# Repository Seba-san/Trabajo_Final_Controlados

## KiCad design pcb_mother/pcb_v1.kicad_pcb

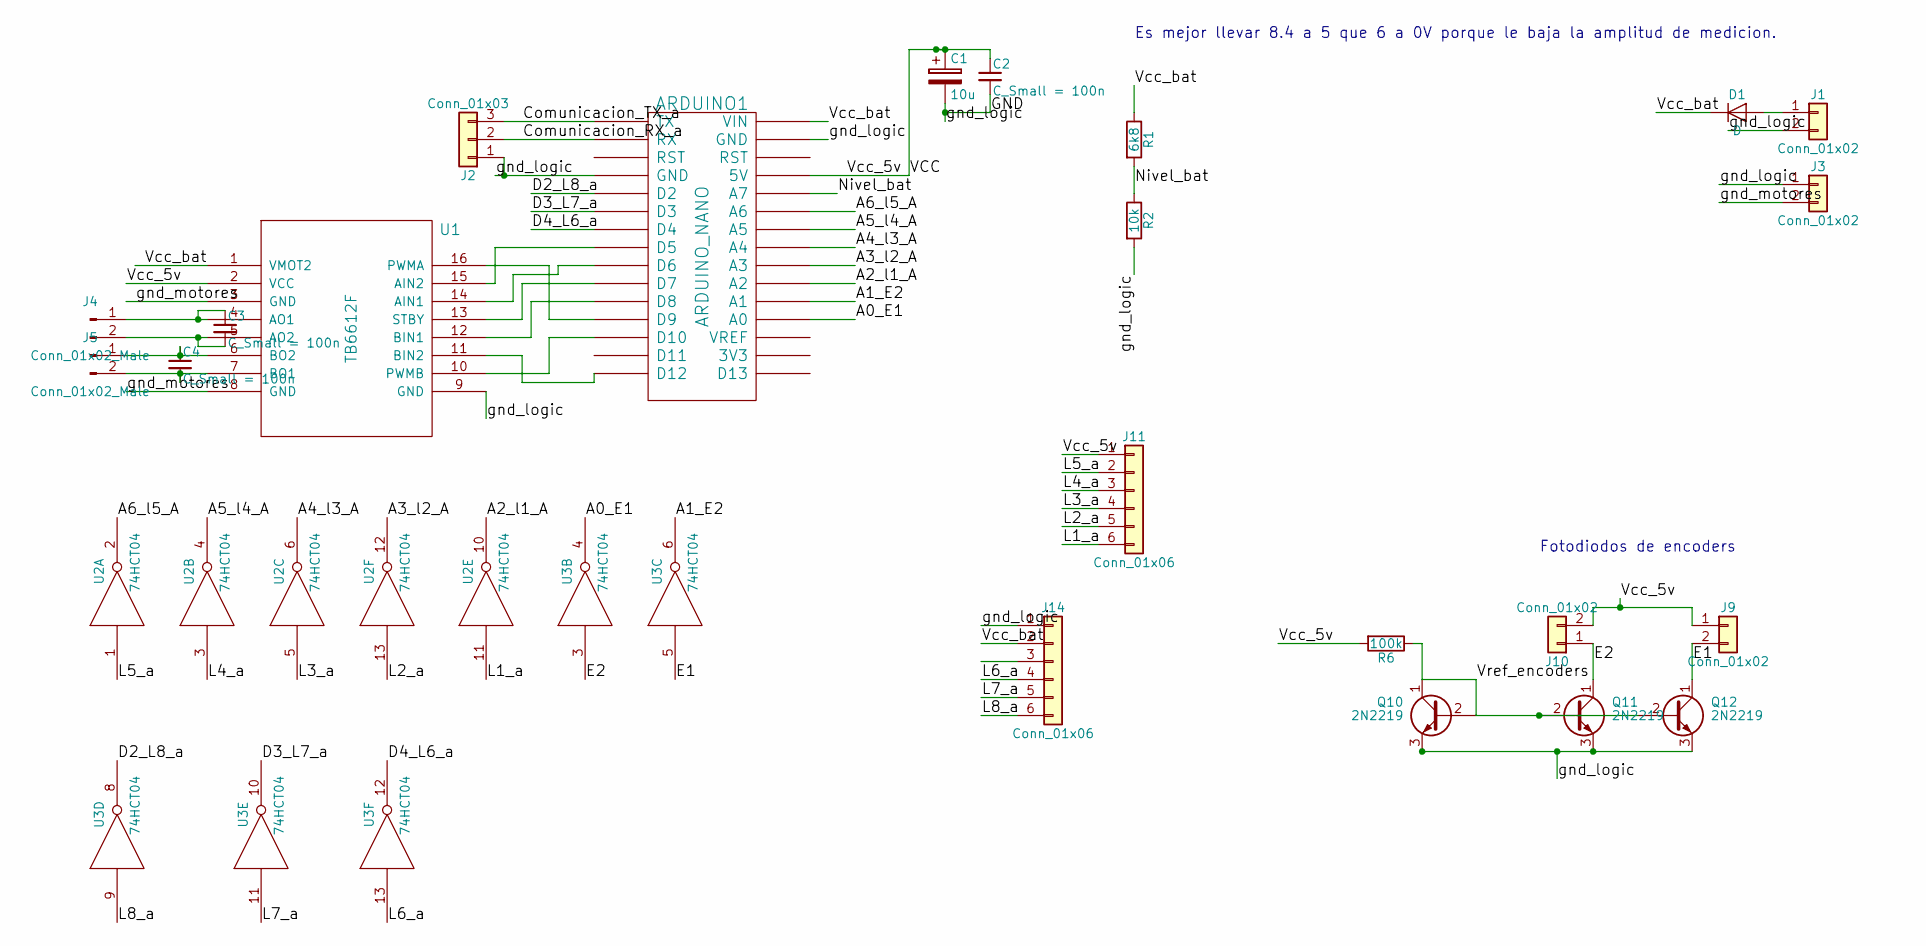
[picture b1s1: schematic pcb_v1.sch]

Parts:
ARDUINO1: ARDUINO_NANO; Arduino_Nano
C1: 10u; CP_Radial_D5.0mm_P2.50mm
C2, C3, C4: C_Small = 100n; C_Disc_D5.0mm_W2.5mm_P2.50mm
D1: D; D_DO-35_SOD27_P7.62mm_Horizontal
J1, J3, J9, J10: Conn_01x02; Pin_Header_Straight_1x02_Pitch2.54mm
J2: Conn_01x03; Pin_Header_Straight_1x03_Pitch2.54mm
J4, J5: Conn_01x02_Male; Pin_Header_Straight_1x02_Pitch2.54mm
J11, J14: Conn_01x06; Pin_Header_Straight_1x06_Pitch2.54mm
Q10, Q11, Q12: 2N2219; TO-92_Inline_Wide
R1: 6k8; R_Axial_DIN0207_L6.3mm_D2.5mm_P10.16mm_Horizontal
R2: 10k; R_Axial_DIN0207_L6.3mm_D2.5mm_P10.16mm_Horizontal
R6: 100k; R_Axial_DIN0207_L6.3mm_D2.5mm_P10.16mm_Horizontal
U1: TB6612F; tb6612
U2, U3: 74HCT04; DIP-14_W7.62mm_Socket_LongPads

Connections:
/A0_E1: ARDUINO1.19 (A0), U3.4
/A1_E2: ARDUINO1.20 (A1), U3.6
/A2_l1_A: ARDUINO1.21 (A2), U2.10
/A3_l2_A: ARDUINO1.22 (A3), U2.12
/A4_l3_A: ARDUINO1.23 (A4), U2.6
/A5_l4_A: ARDUINO1.24 (A5), U2.4
/A6_l5_A: ARDUINO1.25 (A6), U2.2
/Comunicacion_RX_a: ARDUINO1.2 (RX), J2.2
/Comunicacion_TX_a: ARDUINO1.1 (TX), J2.3
/D2_L8_a: ARDUINO1.5 (D2), U3.8
/D3_L7_a: ARDUINO1.6 (D3), U3.10
/D4_L6_a: ARDUINO1.7 (D4), U3.12
/E1: J9.2, Q12.1 (C), U3.5
/E2: J10.1, Q11.1 (C), U3.3
/L1_a: J11.6, U2.11
/L2_a: J11.5, U2.13
/L3_a: J11.4, U2.5
/L4_a: J11.3, U2.3
/L5_a: J11.2, U2.1
/L6_a: J14.4, U3.13
/L7_a: J14.5, U3.11
/L8_a: J14.6, U3.9
/Nivel_bat: ARDUINO1.26 (A7), R1.2, R2.1
/Vcc_bat: ARDUINO1.30 (VIN), D1.1 (K), J14.2, R1.1, U1.1 (VMOT2)
/Vref_encoders: Q10.1 (C), Q10.2 (B), Q11.2 (B), Q12.2 (B), R6.1
/gnd_motores: J3.2, U1.3 (GND), U1.8 (GND)
GND: ARDUINO1.4 (GND), ARDUINO1.29 (GND), C1.2, C2.2, J1.2, J2.1, J3.1, J14.1, Q10.3 (E), Q11.3 (E), Q12.3 (E), R2.2, U1.9 (GND), U2.7 (GND), U3.7 (GND)
unnamed: ARDUINO1.8 (D5), U1.15 (AIN2)
unnamed: ARDUINO1.9 (D6), U1.14 (AIN1)
unnamed: ARDUINO1.10 (D7), U1.13 (STBY)
unnamed: ARDUINO1.11 (D8), U1.12 (BIN1)
unnamed: ARDUINO1.12 (D9), U1.16 (PWMA)
unnamed: ARDUINO1.13 (D10), U1.10 (PWMB)
unnamed: ARDUINO1.15 (D12), U1.11 (BIN2)
unnamed: C3.1, J4.1, U1.4 (AO1)
unnamed: C3.2, J4.2, U1.5 (AO2)
unnamed: C4.1, J5.1, U1.6 (BO2)
unnamed: C4.2, J5.2, U1.7 (BO1)
unnamed: D1.2 (A), J1.1
VCC: ARDUINO1.27 (5V), C1.1, C2.1, J9.1, J10.2, J11.1, R6.2, U1.2 (VCC), U2.14 (VCC), U3.14 (VCC)

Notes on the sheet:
Es mejor llevar 8.4 a 5 que 6 a 0V porque le baja la amplitud de medicion.
Fotodiodos de encoders

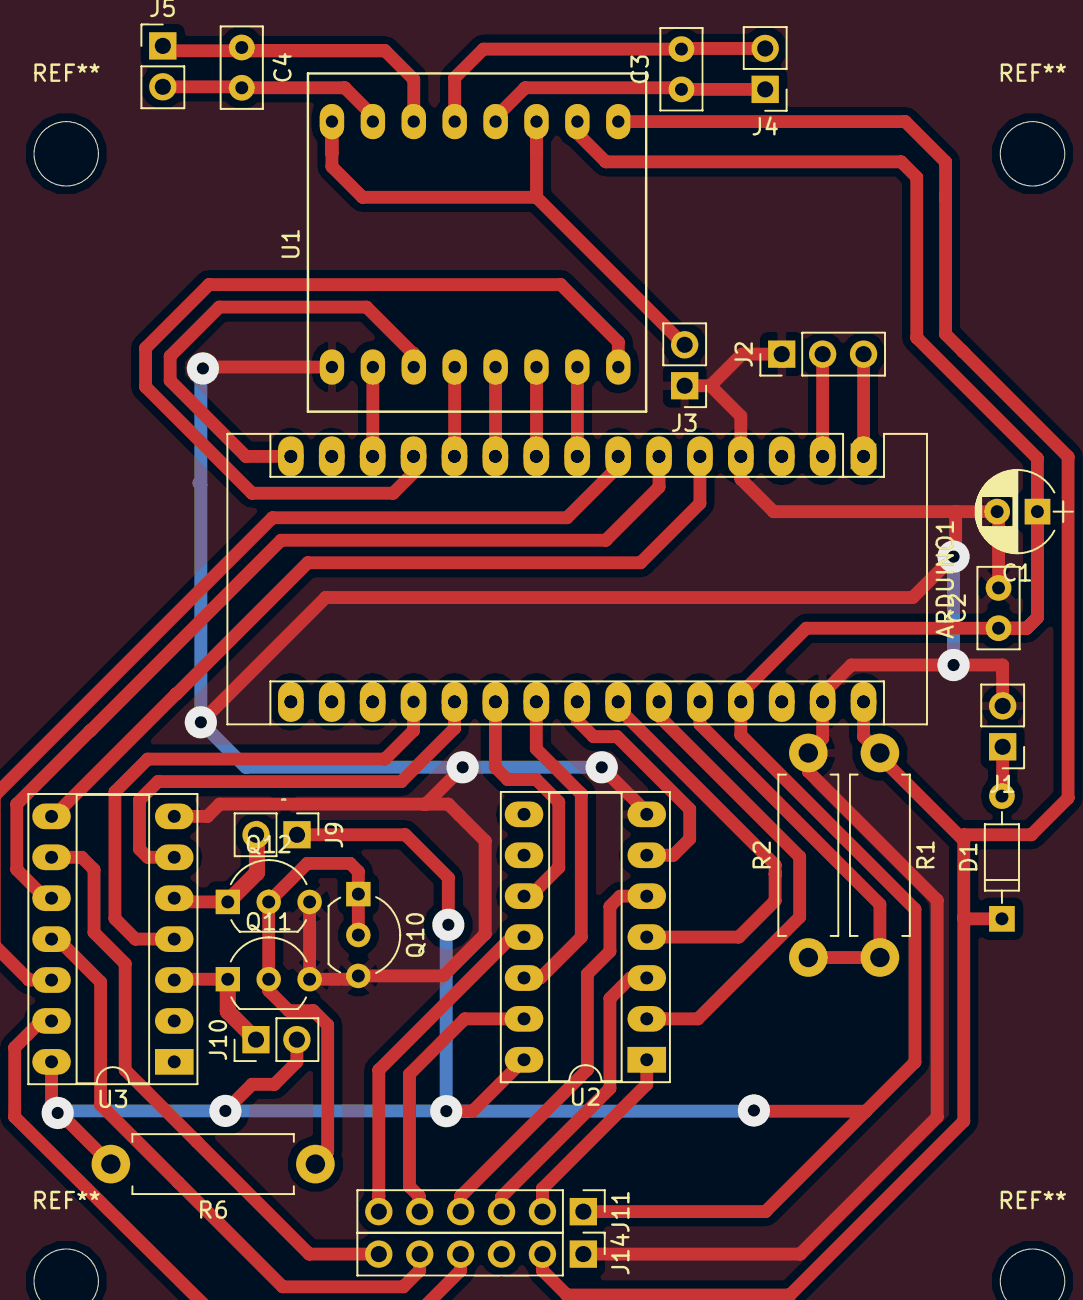
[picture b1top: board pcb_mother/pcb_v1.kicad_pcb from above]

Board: 2 copper layers, 24 parts (0 on the bottom side), 40 nets.

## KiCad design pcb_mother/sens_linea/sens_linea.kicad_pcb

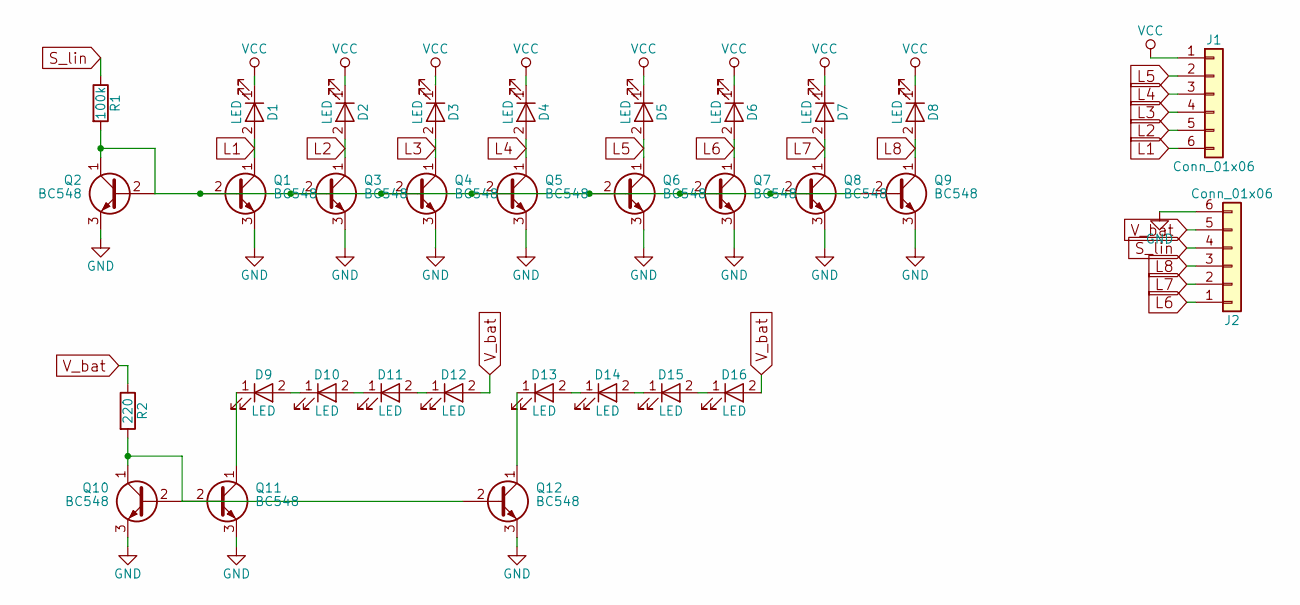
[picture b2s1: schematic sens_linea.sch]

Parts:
D1, D2, D3, D4, D5, D6, D7, D8, D9, D10, D11, D12, D13, D14, D15, D16: LED; LED_D5.0mm
J1, J2: Conn_01x06; Pin_Header_Straight_1x06_Pitch2.54mm
Q1, Q2, Q3, Q4, Q5, Q6, Q7, Q8, Q9, Q10, Q11, Q12: BC548; TO-92_Inline_Wide
R1: 100k; R_Axial_DIN0207_L6.3mm_D2.5mm_P10.16mm_Horizontal
R2: 220; R_Axial_DIN0207_L6.3mm_D2.5mm_P10.16mm_Horizontal

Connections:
GND: J2.6, Q1.3 (E), Q2.3 (E), Q3.3 (E), Q4.3 (E), Q5.3 (E), Q6.3 (E), Q7.3 (E), Q8.3 (E), Q9.3 (E), Q10.3 (E), Q11.3 (E), Q12.3 (E)
L1: D1.2 (A), J1.6, Q1.1 (C)
L2: D2.2 (A), J1.5, Q3.1 (C)
L3: D3.2 (A), J1.4, Q4.1 (C)
L4: D4.2 (A), J1.3, Q5.1 (C)
L5: D5.2 (A), J1.2, Q6.1 (C)
L6: D6.2 (A), J2.1, Q7.1 (C)
L7: D7.2 (A), J2.2, Q8.1 (C)
L8: D8.2 (A), J2.3, Q9.1 (C)
unnamed: D9.1 (K), Q11.1 (C)
unnamed: D9.2 (A), D10.1 (K)
unnamed: D10.2 (A), D11.1 (K)
unnamed: D11.2 (A), D12.1 (K)
unnamed: D13.1 (K), Q12.1 (C)
unnamed: D13.2 (A), D14.1 (K)
unnamed: D14.2 (A), D15.1 (K)
unnamed: D15.2 (A), D16.1 (K)
unnamed: Q1.2 (B), Q2.1 (C), Q2.2 (B), Q3.2 (B), Q4.2 (B), Q5.2 (B), Q6.2 (B), Q7.2 (B), Q8.2 (B), Q9.2 (B), R1.2
unnamed: Q10.1 (C), Q10.2 (B), Q11.2 (B), Q12.2 (B), R2.2
S_lin: J2.4, R1.1
VCC: D1.1 (K), D2.1 (K), D3.1 (K), D4.1 (K), D5.1 (K), D6.1 (K), D7.1 (K), D8.1 (K), J1.1
V_bat: D12.2 (A), D16.2 (A), J2.5, R2.1

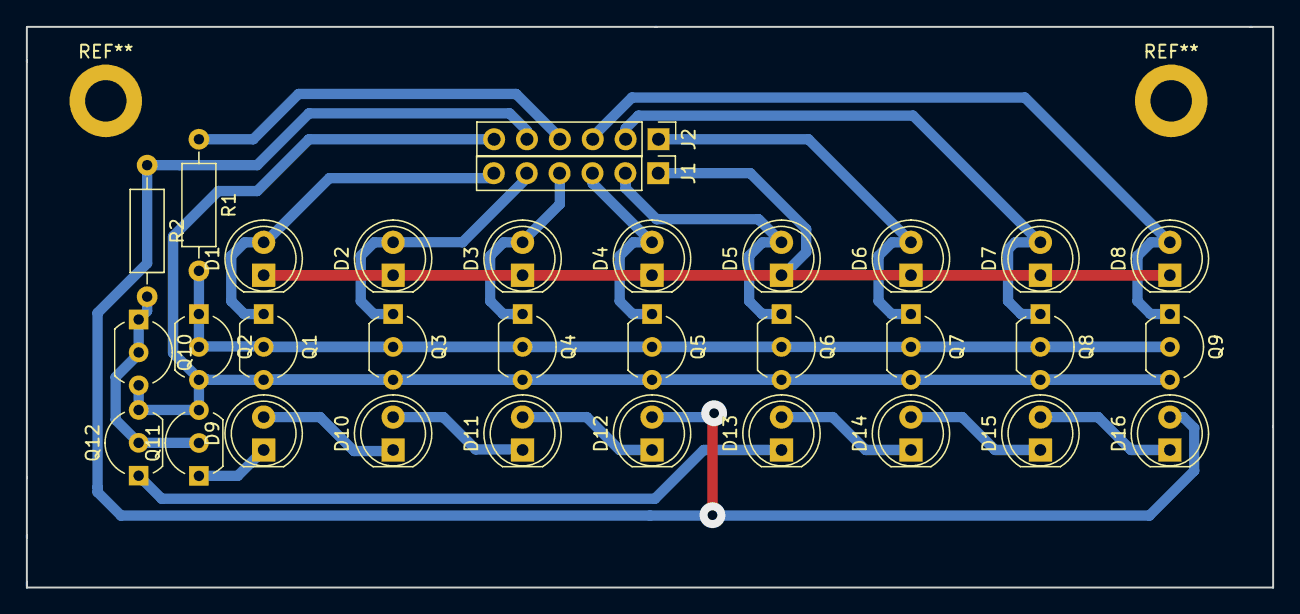
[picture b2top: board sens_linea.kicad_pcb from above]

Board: 2 copper layers, 96.3 x 43.3 mm, 32 parts (0 on the bottom side), 22 nets.

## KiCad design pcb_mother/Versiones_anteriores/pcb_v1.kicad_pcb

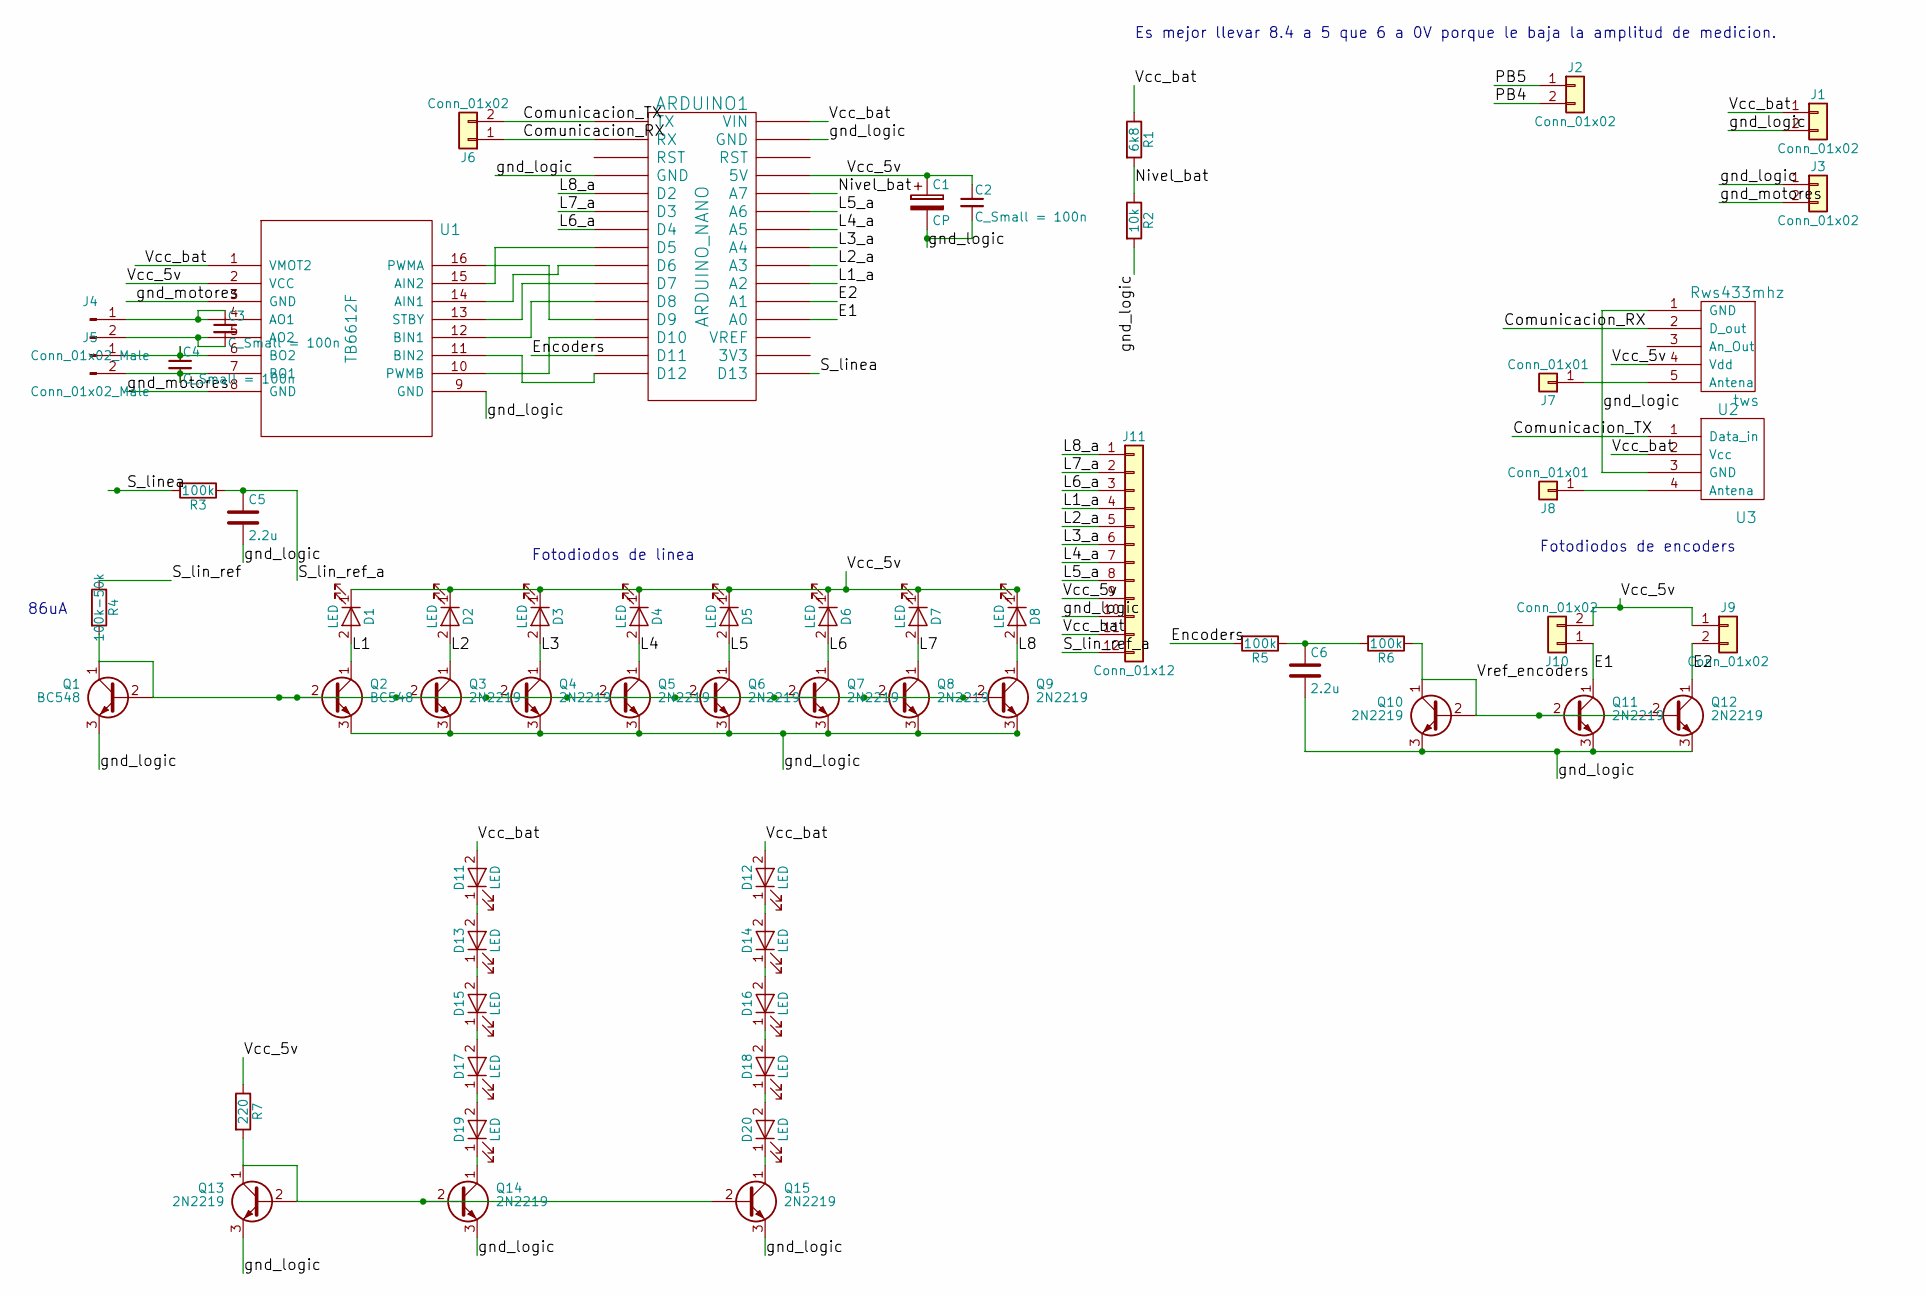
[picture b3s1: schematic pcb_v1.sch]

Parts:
ARDUINO1: ARDUINO_NANO; Arduino_Nano
C1: CP; CP_Radial_D5.0mm_P2.50mm
C2, C3, C4: C_Small = 100n; C_Disc_D5.0mm_W2.5mm_P2.50mm
C5, C6: 2.2u; CP_Radial_D5.0mm_P2.50mm
D1, D2, D3, D4, D5, D6, D7, D8, D11, D12, D13, D14, D15, D16, D17, D18, D19, D20: LED; LED_D5.0mm
J1, J2, J3, J6, J9, J10: Conn_01x02; Pin_Header_Straight_1x02_Pitch2.54mm
J4, J5: Conn_01x02_Male; Pin_Header_Straight_1x02_Pitch2.54mm
J7, J8: Conn_01x01
J11: Conn_01x12; Pin_Header_Straight_1x12_Pitch2.54mm
Q1, Q2: BC548; TO-92_Inline_Wide
Q3, Q4, Q5, Q6, Q7, Q8, Q9, Q10, Q11, Q12, Q13, Q14, Q15: 2N2219; TO-92_Inline_Wide
R1: 6k8; R_Axial_DIN0411_L9.9mm_D3.6mm_P12.70mm_Horizontal
R2: 10k; R_Axial_DIN0411_L9.9mm_D3.6mm_P12.70mm_Horizontal
R3, R5, R6: 100k; R_Axial_DIN0411_L9.9mm_D3.6mm_P12.70mm_Horizontal
R4: 100k-50k; R_Axial_DIN0411_L9.9mm_D3.6mm_P12.70mm_Horizontal
R7: 220; R_Axial_DIN0411_L9.9mm_D3.6mm_P12.70mm_Horizontal
U1: TB6612F; tb6612
U2: Rws433mhz; rws433
U3: tws; tws433

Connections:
/Comunicacion_RX: ARDUINO1.2 (RX), J6.1, U2.2 (D_out)
/Comunicacion_TX: ARDUINO1.1 (TX), J6.2, U3.1 (Data_in)
/E1: ARDUINO1.19 (A0), J10.1, Q11.1 (C)
/E2: ARDUINO1.20 (A1), J9.2, Q12.1 (C)
/Encoders: ARDUINO1.14 (D11), R5.2
/L1: D1.2 (A), Q2.1 (C)
/L1_a: ARDUINO1.21 (A2), J11.4
/L2: D2.2 (A), Q3.1 (C)
/L2_a: ARDUINO1.22 (A3), J11.5
/L3: D3.2 (A), Q4.1 (C)
/L3_a: ARDUINO1.23 (A4), J11.6
/L4: D4.2 (A), Q5.1 (C)
/L4_a: ARDUINO1.24 (A5), J11.7
/L5: D5.2 (A), Q6.1 (C)
/L5_a: ARDUINO1.25 (A6), J11.8
/L6: D6.2 (A), Q7.1 (C)
/L6_a: ARDUINO1.7 (D4), J11.3
/L7: D7.2 (A), Q8.1 (C)
/L7_a: ARDUINO1.6 (D3), J11.2
/L8: D8.2 (A), Q9.1 (C)
/L8_a: ARDUINO1.5 (D2), J11.1
/Nivel_bat: ARDUINO1.26 (A7), R1.2, R2.1
/PB4: J2.2
/PB5: J2.1
/S_lin_ref: R4.1
/S_lin_ref_a: C5.1, J11.12, R3.1
/S_linea: ARDUINO1.16 (D13), R3.2
/Vcc_5v: ARDUINO1.27 (5V), C1.1, C2.1, D1.1 (K), D2.1 (K), D3.1 (K), D4.1 (K), D5.1 (K), D6.1 (K), D7.1 (K), D8.1 (K), J9.1, J10.2, J11.9, R7.1, U1.2 (VCC), U2.4 (Vdd)
/Vcc_bat: ARDUINO1.30 (VIN), D11.2 (A), D12.2 (A), J1.1, J11.11, R1.1, U1.1 (VMOT2), U3.2 (Vcc)
/Vref_encoders: Q10.1 (C), Q10.2 (B), Q11.2 (B), Q12.2 (B), R6.1
/gnd_logic: ARDUINO1.4 (GND), ARDUINO1.29 (GND), C1.2, C2.2, C5.2, C6.2, J1.2, J3.1, J11.10, Q1.3 (E), Q2.3 (E), Q3.3 (E), Q4.3 (E), Q5.3 (E), Q6.3 (E), Q7.3 (E), Q8.3 (E), Q9.3 (E), Q10.3 (E), Q11.3 (E), Q12.3 (E), Q13.3 (E), Q14.3 (E), Q15.3 (E), R2.2, U1.9 (GND), U2.1 (GND), U3.3 (GND)
/gnd_motores: J3.2, U1.3 (GND), U1.8 (GND)
unnamed: ARDUINO1.8 (D5), U1.15 (AIN2)
unnamed: ARDUINO1.9 (D6), U1.14 (AIN1)
unnamed: ARDUINO1.10 (D7), U1.13 (STBY)
unnamed: ARDUINO1.11 (D8), U1.12 (BIN1)
unnamed: ARDUINO1.12 (D9), U1.16 (PWMA)
unnamed: ARDUINO1.13 (D10), U1.10 (PWMB)
unnamed: ARDUINO1.15 (D12), U1.11 (BIN2)
unnamed: C3.1, J4.1, U1.4 (AO1)
unnamed: C3.2, J4.2, U1.5 (AO2)
unnamed: C4.1, J5.1, U1.6 (BO2)
unnamed: C4.2, J5.2, U1.7 (BO1)
unnamed: C6.1, R5.1, R6.2
unnamed: D11.1 (K), D13.2 (A)
unnamed: D12.1 (K), D14.2 (A)
unnamed: D13.1 (K), D15.2 (A)
unnamed: D14.1 (K), D16.2 (A)
unnamed: D15.1 (K), D17.2 (A)
unnamed: D16.1 (K), D18.2 (A)
unnamed: D17.1 (K), D19.2 (A)
unnamed: D18.1 (K), D20.2 (A)
unnamed: D19.1 (K), Q14.1 (C)
unnamed: D20.1 (K), Q15.1 (C)
unnamed: J7.1, U2.5 (Antena)
unnamed: J8.1, U3.4 (Antena)
unnamed: Q1.1 (C), Q1.2 (B), Q2.2 (B), Q3.2 (B), Q4.2 (B), Q6.2 (B), Q7.2 (B), Q8.2 (B), Q9.2 (B), R4.2
unnamed: Q13.1 (C), Q13.2 (B), Q14.2 (B), Q15.2 (B), R7.2

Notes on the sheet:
Fotodiodos de linea
Es mejor llevar 8.4 a 5 que 6 a 0V porque le baja la amplitud de medicion.
Fotodiodos de encoders
86uA

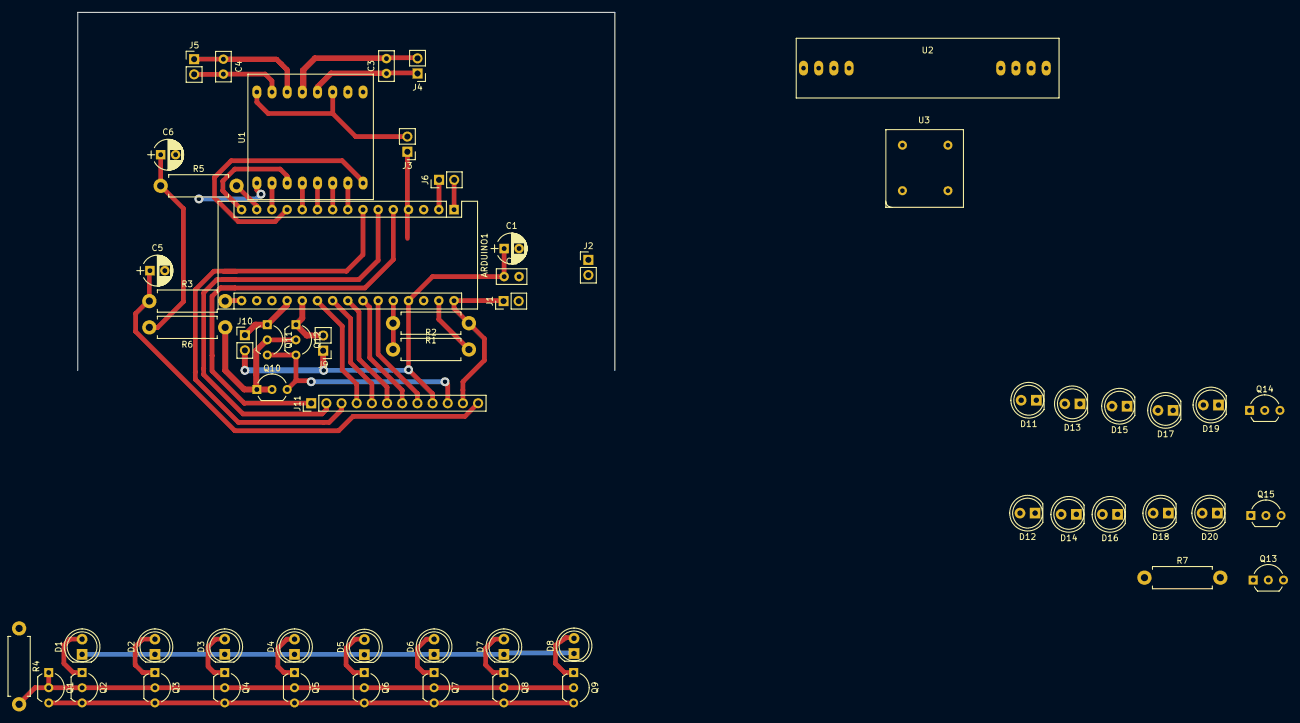
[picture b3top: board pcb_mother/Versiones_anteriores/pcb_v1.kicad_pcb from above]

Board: 2 copper layers, 59 parts (0 on the bottom side), 53 nets.

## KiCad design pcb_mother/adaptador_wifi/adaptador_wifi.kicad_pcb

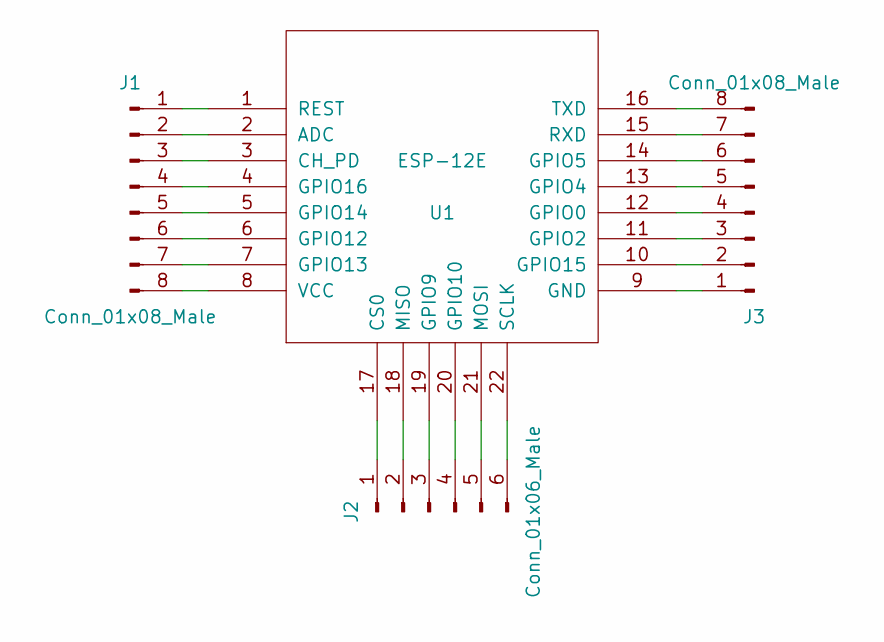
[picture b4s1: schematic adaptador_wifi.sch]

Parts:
J1, J3: Conn_01x08_Male; Pin_Header_Straight_1x08_Pitch2.54mm
J2: Conn_01x06_Male; Pin_Header_Straight_1x06_Pitch2.54mm
U1: ESP-12E; ESP-12E_SMD

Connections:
unnamed: J1.1, U1.1 (REST)
unnamed: J1.2, U1.2 (ADC)
unnamed: J1.3, U1.3 (CH_PD)
unnamed: J1.4, U1.4 (GPIO16)
unnamed: J1.5, U1.5 (GPIO14)
unnamed: J1.6, U1.6 (GPIO12)
unnamed: J1.7, U1.7 (GPIO13)
unnamed: J1.8, U1.8 (VCC)
unnamed: J2.1, U1.17 (CS0)
unnamed: J2.2, U1.18 (MISO)
unnamed: J2.3, U1.19 (GPIO9)
unnamed: J2.4, U1.20 (GPIO10)
unnamed: J2.5, U1.21 (MOSI)
unnamed: J2.6, U1.22 (SCLK)
unnamed: J3.1, U1.9 (GND)
unnamed: J3.2, U1.10 (GPIO15)
unnamed: J3.3, U1.11 (GPIO2)
unnamed: J3.4, U1.12 (GPIO0)
unnamed: J3.5, U1.13 (GPIO4)
unnamed: J3.6, U1.14 (GPIO5)
unnamed: J3.7, U1.15 (RXD)
unnamed: J3.8, U1.16 (TXD)

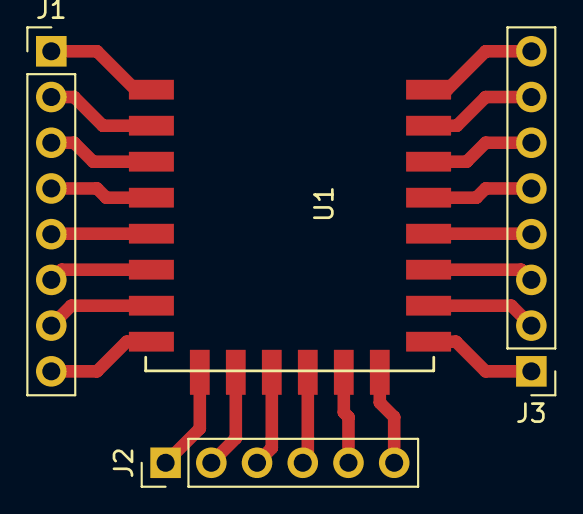
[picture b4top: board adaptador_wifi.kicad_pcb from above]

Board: 2 copper layers, 4 parts (0 on the bottom side), 22 nets.

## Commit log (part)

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2018-04-25 comentario inicial. Este proyecto se genero a partir de otros proyectos, por lo que tienen sus propios comentarios, para tener un mayor orden, decidi (seba) reiniciar el control de versiones. Actualm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
2018-04-26 Cambié de lugar la carpeta de Matlab para que quede todo junto.
2018-04-26 Se cargo el codigo de PID y algunas estructuras de control, sin embargo no se probo. Ademas se borro codigo que no se utilizaba.
2018-04-26 no funciona la comunicacion, vuelvo para atras para ver que paso.
2018-04-30 Se realizaron algunas pruebas con el sistema continuo. Aun no funciona
2018-04-30 Si se multiplica la salida del controlador por una constante que acomode las unidades, es decir, del controlador entran RPM y SALEN RPM, por esto hay que multiplicarlo por una constante para que se t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
2018-05-03 surgio un problema de merge, se corrigio y ahora se commitea
2018-05-03 todo dejo de funcionar, vuelvo para atras
2018-05-03 comento antes de abrir una nueva rama para hacer unas pruebas
2018-05-04 Se estuvieron probando y calibrando nuevamente los motores, PID, etc. Pero se obtiene los mismos resultados.
2018-05-04 Gracias a Cliver supe como agregar las funciones y que compile, todo para ordenar un toque el programa. Ahora falta testearlo.
2018-05-05 Se ajustaron las funciones para que mida correctamente, se calibro con un clock generado con otro arduino a 5mS.
2018-05-09 Se moifico el esquematico y se esta acomodando para poder armar el pcb, la linea que se va a seguir es priorizar el funcionamiento antes que la estetica y el espacio.
2018-05-09 se modificaron las funciones para que funcionen :) seguro que producto del merge final se copiaron cosas que no debian. Hay que mejorar la forma de hacer los merge.... Ademas se creo un script de mat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
2018-05-09 se cambiaron de lugar unas mediciones.
2018-05-10 Pensando sobre linealización
    Agregué un archivo word explicando algunas ideas sobre la linealización. Hay que hacer un ajuste en las variables para que la cosa ande, así como lo hacíamos estaba mal. Todavía no hay nada modificad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
2018-05-10 Ensayo al escalon
    Todos los codigos estan adaptados para que se pueda realizar el ensayo al escalon. Utilizando el codigo de matlab "ensayo_escalon_motor.m"
2018-05-10 Anduvo :D
    Seba encontró la solución mágica: el setpoint se lo dabamos como byte, por eso pedirle w>255 tiraba giladas. Ahora el setpoint va de 10 en 10 (Matlab lo manda dividido 10 y el nano después multiplica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
    Con eso pudimos implementar los controladores P y PI según lo calculado en Simulaciones Planta Contínua y andan (no wow, pero andan). Quedan cositas por entender, pero mantienen la velocidad deseada 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
2018-05-17 se realiza un ultimo chekeo antes de la imprecion.
2018-05-17 Se modificaron los margenes para que sea igual o a penas mas grande (+2mm). Esta version SI se imprimio, la anterior no, porque era muy grande.
2018-05-18 Limpieza paso inicial
    La idea es borrar todo lo que no sea indispensable del código que implementa un PID en los motores. Por ahora lo único que hice es guardar una réplica del código en la carpeta Ensayo_escalon_y_PID_mo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
2018-05-23 Agregamos jaula
    Ahora los dos motores tienen la jaulita. Se probó ver la respuesta de un motor y después del otro. Parece andar, pero con los valores de control puestos se ve que el motor de la derecha no responde t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
2018-05-23 Se realizo el ensayo al escalon asincronico con las jaulas.
2018-05-23 Ensayo Escalon de Ambos Motores
    Se le agregó los resultados de los ensayos al escalón de ambos motores.
2018-05-24 se hicieron algunas pocas correciones, pero casi no afectan.
2018-05-25 Acomodando Sensor de Línea
2018-05-25 Se agrego a la comunicacion la posibilidad de cambiar el k del PID. se creo la funcion K_inestable y se descargaron algunos pdf esclarecedores.
2018-05-25 Andando (ponele)
    Bueno, ahí nos tira para bajas velocidades (<10) los tiempos que va midiendo (último valor de bufferVelB), estando la mitad aprox cerca de un valor y la otra mitad cerca de otro mayor.
2018-05-25 Sospechoso
    Le pedí que me envíe el valor de "suma" para calcular yo la frec angular y da extremadamente bien...
2018-05-25 Ensayo Escalón con Medición Corregida
    Da re sexy :') . Ahora seguimos.
2018-05-26 se verificaron los pines del sensor de linea y su contrapartida en el codigo, todo tiene sentido. Hay que descomentar la parte de la lectura y arreglarla para que funcione.
2018-05-28 hago un commit para recuperar la medicion respuesta_escalon_motorB180523193004.mat
2018-05-29 se agrego el otro metodo de Cogen Coen segun el pdf que nos paso Daniel. Este nuevo metodo con tangente=0 da parametros distintos a los de antes con el PI
2018-05-29 Se probo el controlador CC en el modo PI para 500 RPM y funciona muy bien, para 300 RPM actua subamortiguado
2018-05-29 Acomodando Variables para la implementacion del PID final
    Eso.
2018-05-30 Agrego un archivo de texto que habia quedado perdido en otro branch
2018-05-30 se diseñaron un par de filtros para filtrar la señal, para que de esta manera se evite hacer una media movil. No hubo exito. Ademas se levanto la 180530150723respuesta_escalon_motorB_sin_promedio_10_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
2018-05-30 Se acomodo un poco el codigo 'Simulando_planta.m' para que sea un poco mas intuitivo realizar el ajuste. Hay que estimar nuevamente los retardos del sistema.
2018-05-30 Explotó todo :'(
    Terminé de armar el código que mediría el ensayo al escalón de los motores offline. El tema es que no anda nada T-T . Parecería que por algún extraño motivo no está andando la generación de los PWM :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
2018-05-31 Arreglado :D
2018-06-01 Los Ensayos andan
    Estuvimos probando los ensayos y los guardamos. Anda muy bien. Después probamos ponerle un controlador calculado hace mucho y vimos cómo anda. Se nota que está mal calibrado, pero la medición muestra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
    Después me puse a modificar el código de ensayo escalón del sist total. Mientras comparaba códigos toqué un par de detalles del de los motores sin darme cuenta que no había commiteado....espero que n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
2018-06-01 Ensayo total escrito, no testeado
    Terminé de armar el código. Falta probar
2018-06-01 Probando
    Probamos el código del ensayo al escalón. Hay que mejorarlo para facilitar el ensayo.
2018-06-01 se esta afinando el sensor de linea para realizar el escalon
2018-06-01 Ensayo Escalón exitoso :D
    Tira bien :)
2018-06-02 Probando K
    Le puse un K inventado, parece que no anda.
    Esta en Sistema_Total_Prueba
2018-06-02 Se hicieron minimos cambios para poder hacer andar el P en la medicion del angulo, ahora cambio de rama.
2018-06-02 creo que encontre la solucion: por medio de un k negativo, hacer el sistema estable y luego a ese nuevo sistema aplicarle el controlador. Por la naturaleza del sistema creo que el K de realimentacion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
2018-06-02 Logre estimar el sistema INESTABLE y lo logro estavilizar por medio del PID tuner. tiene un polo en 9.47 y la ganancia es 0.094 o 0.062
2018-06-02 Probando estimar el sist total
2018-06-02 se cargo el modelos.mat
2018-06-03 Prueba controlador PI
    Oscila bocha
2018-06-04 comentario previo a hacer un cambio profundo
2018-06-04 Consegui levantar el modelo considerando beta como entrada y delta W como salida, por medio de sistemas inversos quizas se pueda hacer la estimacion inversa :=). El modelo es sysb_dw del archivo ../.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
2018-06-04 se cargaron todos los ensayos con algunas correcciones de dW.
2018-06-05 Dando vueltas
    No sé ni qué hice desde el último commit
2018-06-05 We are the champions,my friends!'n we'll keep on fighting till the end!
    Le pusimos Tf=20*Kd y el PID tuner tiró ctes razonables. Probamos con eso y pudo girar!!! (Las ctes usadas eran: {196.762,-393.4536,196.6916,1.9999,-0.99994} )
2018-06-06 probando estimar beta pero sin exito
2018-06-06 Que se yo
2018-06-06 commit previo a ensayos escalón
2018-06-06 Ensayo corregido
    Le recalculé el beta a partir del byte del sensor porque estaba usando los valores del ensayo viejo
2018-06-08 Acomodo de acentos para Seba
2018-06-11 Se realizo un pre-pre informe, falta realizar mediciones con el dispositivo con carga. edgardo me dijo que si se detecta un sobreimpulso en las PWM quiere decir (no directamente) que hay drift
2018-06-11 nada 2
2018-06-11 Arreglos de Seba - no funciono
2018-06-12 Se creo la funcion generica para transmitir los datos, pero hay conflictos para los tipos de datos. Funciona biencon int
2018-06-15 Probando armar un GUIDE en Matlab
    Andan las boludeces, falta ver cómo se comporta con el nano.
2018-06-21 Se esta realizando una adaptacion en la comunicacion para poder utilizar los modulitos de bluetooth, ya que posee un canal real de comunicacion de 8000 bps; tiene un buffer muy grande lo que permite 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
2018-06-21 Se hicieron las mediciones sin controlador de motores y con controlador de motores. Por triste que suene, cuando se intenta estimar la planta con los datos con carga, las estimaciones dan bastante ma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
2018-06-22 Con estos programas se esta haciendo los ensayos al escalon para caracterizar el sistema
2018-06-23 Ya se realizaron todos los ensayos, ahora falta interpretarlos y agregarlos al informe.
2018-06-24 Cambio de rama para realizar nuevas mediciones
2018-06-25 Se modifico un poco el informe, pero sin ganas, hay que revisar las ecuaciones las hipotesis aplicadas. Tambien hay que revisar la redaccion, ya no es copia literal de lo que estaba antes.
2018-06-25 comentario antes de hacer un merge para trabajar en paralelo con TSF.
2018-06-26 Escribiendo sobre encoders
2018-06-26 Escribiendo sobre el sensor de línea
2018-06-27 comentario basura
2018-07-02 Commit previo al intento de merge
2018-07-06 Trabajando 2
2018-07-10 Se avanzo con la simulacion del bicho. Se logro simular las curvas, ademas los parametros son muy parecidos. Faltaria modificar el modelo del sensor, esto es: dado el vector de estados estimar la med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
2018-07-11 Pequeño reajuste de estructura
2018-07-13 Se completo la parte de discretizacion del PID, tiene algunos errores (tambien de ortografia), por lo que hay que releerlo y verificarlo. Falta agregar algunas imagenes, establecer como fue el ajuste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
2018-07-18 Estuve reordenando un poco las carpetas. Ademas comence a probar distintos controladores PIDF para hacer los ensayos proximamente. El codigo usado esta al final de simulando_planta
2018-07-18 comentario basura, para no hacer un ammend (no funcionan bien los ammend)
2018-07-20 Se modifiracon algunas cosas, basicamente se cambio la linea 262 de controlados.cpp round(float(sumaPonderada/suma))
2018-07-22 Se estan modificando el codigo de arduino, detectamos que tiene error en estado estacionario y presentaba algunas cosas erraticas. Ademas se agrego el codigo para que lea el valo de la bateria.
2018-07-22 confirmado, ahora hay que buscar los PIDF tal que generen un delta omega lo suficientemente grande como para soportar el radio de giro de la pista (43 cm o menos).
2018-07-22 nuevos contrladores con esfuerzos mayores
2018-07-25 se modifico levemente algunas cosas que decia el informe y ademas se agrego la parte del control total. Este comentario es previo a pońer la tabla de los resultados.
2018-07-26 Este controlador es el que mejor funciona hasta la fecha. PIDF 0.25 y 0.51 en PID Tuner
2018-07-29 Se realizó una lectura completa del trabajo sumado a todas las correcciones pertinentes; se cambiaron algunas imagenes, las dimenciones de otras...
2018-07-29 se modifico la tabla de los resultados y se agrego texto en esa parte. No me convence mucho la precentacion de los resutlados, pero creo que es similar a la de otros trabajos.
2018-08-01 Modificaciones al Informe terminado
    Hice varias modificaciones menores y otras no tanto. Las que no eran menores en general las deje comentadas, asi como un par de cosas que no me cerraron o que creo que habria que mejorar. Todos esos 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
